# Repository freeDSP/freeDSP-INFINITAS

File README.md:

# freeDSP Infinitas

USB Audio Class 2 compliant audio interface with up to 32 input and up to 32 output channels and optional ADAU1452 DSP.

BOARD STATUS: RELEASED!

MAIN COORDINATOR: [dspverden](https://github.com/dspverden)

DOCUMENTATION: [Getting Started](https://docs.google.com/document/d/1jxKOcB1Af_6xawysrgFLgatrspSJ-aYZdDhTxlWoG2I)

IMPORTANT:

Please take care on which branch you're currently working!

Branches:

master - this branch always holds the latest released revision

develop - this is the develop branch with new features

## License
This work is licensed under <br />Dieses Werk ist lizenziert unter einer <a rel="license" href="http://creativecommons.org/licenses/by-nc-sa/4.0/">Creative Commons Namensnennung - Nicht-kommerziell - Weitergabe unter gleichen Bedingungen 4.0 International Lizenz</a>.

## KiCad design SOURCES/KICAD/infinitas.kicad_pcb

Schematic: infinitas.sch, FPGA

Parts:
B101, B102, B103, B104, B105, B106: TEST_1P; MountingHole_3.2mm_M3_DIN965_Pad
C101, C103, C104, C105, C106, C107, C108, C109, C110, C111, C112, C113, C114, C115, C116, C117, C118, C119, C120, C121, C124, C126, C129, C132: CAP_100n_50V_X7R_0805; C0805-X7R; digikey 399-1170-1-ND
C102, C122, C125, C127, C128, C130, C131, C133: CAP_10u0_25V_X5R_0805; C0805-X7R; digikey 490-10748-1-ND
C123: CAP_22u0_10V_X5R_0805; C0805-X7R; digikey 490-10511-1-ND
IC101: IC_CS2100CP; MSOP-10_3x3mm_Pitch0.5mm; digikey 598-1750-ND
IC102, IC103: IC_PCA9545APW; TSSOP-20_4.4x6.5mm_Pitch0.65mm; digikey 568-1865-1-ND
IC104: IC_LCMXO2-1200HC-6TG144C; TQFP-144_20x20mm_Pitch0.5mm; digikey 220-2040-ND
IC105: IC_TLV62565; SOT-23-5; digikey 296-43657-1-ND
IC106: IC_ADM811TARTZ; SOT-143; digikey ADM811TARTZ-REELCT-ND
IC107: IC_LM1117MP-5.0; SOT223; digikey LM1117MP-5.0/NOPBCT-ND
IC108, IC109: IC_NCP1117LPST33; SOT223; digikey NCP1117LPST33T3GOSCT-ND
L101: IND_2U20_30%_4A5; MCSDRH73B; digikey 811-1157-1-ND
OSC101: OSC_24M576; ASFL1; digikey 300-8253-1-ND
R101: RES_10K0_1%_0.125W_Thick_0805; C0805-RES; digikey 311-10.0KCRCT-ND
R102, R103, R104, R105, R112, R113, R114, R115, R124, R125, R126, R127, R134, R135, R136, R137: RES_2K00_1%_0.125W_Thick_0805; C0805-RES; digikey 311-2.00KCRCT-ND
R106, R107, R108, R109, R110, R111, R128, R129, R130, R131, R132, R133: RES_47K0_1%_0.125W_Thick_0805; C0805-RES; digikey 311-47.0KCRCT-ND
R116, R117, R122, R142, R144, R146, R149: RES_51R0_1%_0.125W_Thick_0805; C0805-RES; digikey 311-51.0CRCT-ND
R118: RES_4K70_1%_0.125W_Thick_0805; C0805-RES; digikey 311-4.70KCRCT-ND
R119, R120, R121, R123, R138, R139, R140, R141, R143, R145, R147, R148, R150, R151, R152: RES_51R0_5%_4x0603; R_Array_Convex_4x0603; digikey TC164J-51CT-ND
R153: RES_1K00_1%_0.125W_Thick_0805; C0805-RES; digikey 311-1.00KCRCT-ND
R154: RES_80K6_1%_0.125W_Thick_0805; C0805-RES; digikey 311-80.6KCRCT-ND
R155: RES_100K_1%_0.125W_Thick_0805; C0805-RES; digikey 311-100KCRCT-ND
R156: RES_120K_1%_0.125W_Thick_0805; C0805-RES; digikey 311-120KCRCT-ND
X101: CON_HDR_02x04; HDR_02x04; digikey 952-3276-ND
X102, X103: CON_IDC64; IDC64; digikey ED10532-ND
X104: CON_MicroMatch-10G; MM-10G; digikey A110869-ND
X105: CON_MicroFit3_02x02; Microfit3_43045-0428; digikey WM10670-ND

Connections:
+1V0: C123.1, L101.2, R154.1; also elsewhere on the board
+3V3: C101.2, C102.2, C103.2, C104.2, C106.2, C107.2, C108.2, C109.2, C110.2, C111.2, C112.2, C113.2, C114.2, C115.2, C116.2, C117.2, C118.2, C119.2, C120.2, C121.2, C132.2, C133.2, IC101.1, IC102.2, IC102.20, IC104.7, IC104.16, IC104.30, IC104.36, IC104.37, IC104.51, IC104.66, IC104.72, IC104.79, IC104.88, IC104.102, IC104.108, IC104.118, IC104.123, IC104.135, IC104.144, IC109.2, IC109.4, OSC101.4, R101.2, R102.2, R103.2, R104.2, R105.2, R106.2, R107.2, R108.2, R109.2, R110.2, R111.2, R112.2, R113.2, R114.2, R115.2, X101.5, X101.7; also elsewhere on the board
+5V: C122.2, C126.2, C127.2, IC105.1, IC105.4, IC107.2, IC107.4, X104.1, X104.2; also elsewhere on the board
+12V: C125.2, C128.2, C131.2, IC107.3, IC108.3, IC109.3, X102.1, X102.17, X102.33, X102.49, X103.1, X103.17, X103.33, X103.49, X105.1, X105.2
/BCLK:1: R143.6, X102.7
/BCLK:2: R152.6, X103.7
/BCLK:3: R141.6, X102.23
/BCLK:4: R148.6, X103.23
/BCLK:5: R139.6, X102.39
/BCLK:6: R147.6, X103.39
/BCLK:7: R123.6, X102.55
/BCLK:8: R145.6, X103.55
/BCLKIN0: R119.4; also elsewhere on the board
/BCLKIN1: R119.1; also elsewhere on the board
/BCLKIN2: R120.2; also elsewhere on the board
/BCLKIN3: R121.3; also elsewhere on the board
/BCLKOUT0: R140.7; also elsewhere on the board
/BCLKOUT1: R140.5; also elsewhere on the board
/BCLKOUT2: R138.7; also elsewhere on the board
/BCLKOUT3: R138.5; also elsewhere on the board
/CLKREF: IC101.7, R144.1
/LRCK:1: R143.7, X102.9
/LRCK:2: R152.7, X103.9
/LRCK:3: R141.7, X102.25
/LRCK:4: R148.7, X103.25
/LRCK:5: R139.7, X102.41
/LRCK:6: R147.7, X103.41
/LRCK:7: R123.7, X102.57
/LRCK:8: R145.7, X103.57
/LRCKIN0: R119.3; also elsewhere on the board
/LRCKIN1: R120.4; also elsewhere on the board
/LRCKIN2: R120.1; also elsewhere on the board
/LRCKIN3: R121.2; also elsewhere on the board
/LRCKOUT0: R140.8; also elsewhere on the board
/LRCKOUT1: R140.6; also elsewhere on the board
/LRCKOUT2: R138.8; also elsewhere on the board
/LRCKOUT3: R138.6; also elsewhere on the board
/MCLK: R142.1; also elsewhere on the board
/MCLK:1: R143.8, X102.15
/MCLK:2: R152.8, X103.15
/MCLK:3: R141.8, X102.31
/MCLK:4: R148.8, X103.31
/MCLK:5: R139.8, X102.47
/MCLK:6: R147.8, X103.47
/MCLK:7: R123.8, X102.63
/MCLK:8: R145.8, X103.63
/MDI:1: IC104.91, X102.3
/MDI:2: IC104.61, X103.3
/MDI:3: IC104.96, X102.19
/MDI:4: IC104.69, X103.19
/MDI:5: IC104.104, X102.35
/MDI:6: IC104.75, X103.35
/MDI:7: IC104.110, X102.51
/MDI:8: IC104.82, X103.51
/MDO:1: R143.5, X102.5
/MDO:2: R152.5, X103.5
/MDO:3: R141.5, X102.21
/MDO:4: R148.5, X103.21
/MDO:5: R139.5, X102.37
/MDO:6: R147.5, X103.37
/MDO:7: R123.5, X102.53
/MDO:8: R145.5, X103.53
/OSC: IC104.19, R117.2
/PLLCLK: IC104.27, R116.1
/PLLLOCKED: IC101.4, IC104.28
/SCL: IC101.9, IC102.18, IC103.18, IC104.126; also elsewhere on the board
/SCL:1: IC102.16, R112.1, X102.13
/SCL:2: IC103.13, R136.1, X103.13
/SCL:3: IC102.13, R114.1, X102.29
/SCL:4: IC103.16, R134.1, X103.29
/SCL:5: IC102.9, R102.1, X102.45
/SCL:6: IC103.6, R126.1, X103.45
/SCL:7: IC102.6, R104.1, X102.61
/SCL:8: IC103.9, R124.1, X103.61
/SDA: IC101.10, IC102.19, IC103.19, IC104.125; also elsewhere on the board
/SDA:1: IC102.15, R113.1, X102.11
/SDA:2: IC103.12, R137.1, X103.11
/SDA:3: IC102.12, R115.1, X102.27
/SDA:4: IC103.15, R135.1, X103.27
/SDA:5: IC102.8, R103.1, X102.43
/SDA:6: IC103.5, R127.1, X103.43
/SDA:7: IC102.5, R105.1, X102.59
/SDA:8: IC103.8, R125.1, X103.59
/SPDIFIN: IC104.48, X104.9
/SPDIFOUT: R150.5, X104.7
/TCK: IC104.131, R118.2, X101.3
/TDI: IC104.136, X101.1
/TDMIN0: R119.2; also elsewhere on the board
/TDMIN1: R120.3; also elsewhere on the board
/TDMIN2: R121.4; also elsewhere on the board
/TDMIN3: R121.1; also elsewhere on the board
/TDMOUT0: IC104.12; also elsewhere on the board
/TDMOUT1: IC104.11; also elsewhere on the board
/TDMOUT2: IC104.143; also elsewhere on the board
/TDMOUT3: IC104.142; also elsewhere on the board
/TDO: IC104.137, X101.6
/TMS: IC104.130, X101.4
/WCLKIN: IC104.59, X104.5
/WCLKOUT: R149.1, X104.3
/WCLKREF: IC101.5, R146.1
/XBCLK: R151.7; also elsewhere on the board
/XLRCK: R151.8; also elsewhere on the board
/XMCLK: R150.6; also elsewhere on the board
/XTDMIN1: R151.6; also elsewhere on the board
/XTDMIN2: R151.5; also elsewhere on the board
/XTDMIN3: R150.8; also elsewhere on the board
/XTDMIN4: R150.7; also elsewhere on the board
/XTDMOUT1: IC104.43; also elsewhere on the board
/XTDMOUT2: IC104.44; also elsewhere on the board
/XTDMOUT3: IC104.45; also elsewhere on the board
/XTDMOUT4: IC104.47; also elsewhere on the board
/dspSPDIFIN: R122.1; also elsewhere on the board
/dspSPDIFOUT: IC104.115; also elsewhere on the board
/~RST: IC104.42, IC106.2, R155.2; also elsewhere on the board
/~USBRST: R153.1; also elsewhere on the board
GND: C101.1, C102.1, C103.1, C104.1, C105.1, C106.1, C107.1, C108.1, C109.1, C110.1, C111.1, C112.1, C113.1, C114.1, C115.1, C116.1, C117.1, C118.1, C119.1, C120.1, C121.1, C122.1, C123.2, C124.1, C125.1, C126.1, C127.1, C128.1, C129.1, C130.1, C131.1, C132.1, C133.1, IC101.2, IC101.8, IC102.1, IC102.10, IC103.1, IC103.2, IC103.10, IC104.8, IC104.18, IC104.29, IC104.46, IC104.53, IC104.64, IC104.80, IC104.90, IC104.101, IC104.116, IC104.124, IC104.134, IC105.2, IC106.1, IC107.1, IC108.1, IC109.1, OSC101.2, R118.1, R155.1, R156.1, X101.8, X102.2, X102.4, X102.6, X102.8, X102.10, X102.12, X102.14, X102.16, X102.18, X102.20, X102.22, X102.24, X102.26, X102.28, X102.30, X102.32, X102.34, X102.36, X102.38, X102.40, X102.42, X102.44, X102.46, X102.48, X102.50, X102.52, X102.54, X102.56, X102.58, X102.60, X102.62, X102.64, X103.2, X103.4, X103.6, X103.8, X103.10, X103.12, X103.14, X103.16, X103.18, X103.20, X103.22, X103.24, X103.26, X103.28, X103.30, X103.32, X103.34, X103.36, X103.38, X103.40, X103.42, X103.44, X103.46, X103.48, X103.50, X103.52, X103.54, X103.56, X103.58, X103.60, X103.62, X103.64, X104.4, X104.6, X104.8, X104.10, X105.3, X105.4; also elsewhere on the board
unnamed: IC101.3, R116.2
unnamed: IC102.3, R108.1
unnamed: IC102.4, R107.1
unnamed: IC102.7, R106.1
unnamed: IC102.11, R111.1
unnamed: IC102.14, R110.1
unnamed: IC102.17, R109.1
unnamed: IC103.3, R130.1
unnamed: IC103.4, R129.1
unnamed: IC103.7, R128.1
unnamed: IC103.11, R133.1
unnamed: IC103.14, R132.1
unnamed: IC103.17, R131.1
unnamed: IC104.1, R138.4
unnamed: IC104.2, R138.3
unnamed: IC104.3, R138.2
unnamed: IC104.4, R138.1
unnamed: IC104.5, R140.4
unnamed: IC104.6, R140.3
unnamed: IC104.9, R140.2
unnamed: IC104.10, R140.1
unnamed: IC104.13, R142.2
unnamed: IC104.20, R144.2
unnamed: IC104.32, R146.2
unnamed: IC104.49, R150.4
unnamed: IC104.50, R150.3
unnamed: IC104.52, R150.2
unnamed: IC104.54, R150.1
unnamed: IC104.55, R151.4
unnamed: IC104.56, R151.3
unnamed: IC104.57, R151.2
unnamed: IC104.58, R151.1
unnamed: IC104.60, R149.2
unnamed: IC104.62, R152.4
unnamed: IC104.65, R152.3
unnamed: IC104.67, R152.2
unnamed: IC104.68, R152.1
unnamed: IC104.70, R148.4
unnamed: IC104.71, R148.3
unnamed: IC104.73, R148.2
unnamed: IC104.74, R148.1
unnamed: IC104.76, R147.4
unnamed: IC104.77, R147.3
unnamed: IC104.78, R147.2
unnamed: IC104.81, R147.1
unnamed: IC104.83, R145.4
unnamed: IC104.84, R145.3
unnamed: IC104.85, R145.2
unnamed: IC104.86, R145.1
unnamed: IC104.92, R143.4
unnamed: IC104.93, R143.3
unnamed: IC104.94, R143.2
unnamed: IC104.95, R143.1
unnamed: IC104.97, R141.4
unnamed: IC104.98, R141.3
unnamed: IC104.99, R141.2
unnamed: IC104.100, R141.1
unnamed: IC104.105, R139.4
unnamed: IC104.106, R139.3
unnamed: IC104.107, R139.2
unnamed: IC104.109, R139.1
unnamed: IC104.111, R123.4
unnamed: IC104.112, R123.3
unnamed: IC104.113, R123.2
unnamed: IC104.114, R123.1
unnamed: IC104.117, R122.2
unnamed: IC104.119, R121.8
unnamed: IC104.120, R121.7
unnamed: IC104.121, R121.6
unnamed: IC104.122, R121.5
unnamed: IC104.127, R120.8
unnamed: IC104.128, R120.7
unnamed: IC104.132, R120.6
unnamed: IC104.133, R120.5
unnamed: IC104.138, R119.8
unnamed: IC104.139, R119.7
unnamed: IC104.140, R119.6
unnamed: IC104.141, R119.5
unnamed: IC105.3, L101.1
unnamed: IC105.5, R154.2, R156.2
unnamed: IC106.3, R153.2
unnamed: OSC101.1, R101.1
unnamed: OSC101.3, R117.1
VDD: C105.2, C124.2, C129.2, C130.2, IC103.20, IC106.4, IC108.2, IC108.4, R124.2, R125.2, R126.2, R127.2, R128.2, R129.2, R130.2, R131.2, R132.2, R133.2, R134.2, R135.2, R136.2, R137.2; also elsewhere on the board

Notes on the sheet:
I2C_ADDR: 0xE2
I2C_ADDR: 0xE0

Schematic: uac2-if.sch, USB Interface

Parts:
C201: CAP_10n0_50V_X7R_0805; C0805-X7R; digikey 311-1136-1-ND
C202, C203, C204, C207: CAP_100n_50V_X7R_0805; C0805-X7R; digikey 399-1170-1-ND
C205, C206: CAP_10u0_25V_X5R_0805; C0805-X7R; digikey 490-10748-1-ND
C208: CAP_1n00_50V_X7R_0805; C0805-X7R; digikey 399-1147-1-ND
C209, C210, C211, C212, C213, C214, C215, C216, C217, C218, C219, C220, C221, C222, C223, C224, C225, C226, C227, C228, C229, C230, C231, C232, C233: CAP_100n_10V_X7R_0402; C_0402; digikey 490-6321-1-ND
D201: DIO_MBR120VLSFT; SOD123; digikey MBR120VLSFT3GOSCT-ND
IC201: IC_XE216-512-TQ128; TQFP-128_14x14mm_Pitch0.4mm_EP_Handsoldering; digikey 880-1096-ND
IC202: IC_NCP4681DSQ25T1G; SC-70-5; digikey NCP4681DSQ25T1GOSCT-ND
IC203: IC_IS25LP080D; SOIC8_3.9x4.9mm_Pitch1.27mm; digikey 706-1580-ND
IC204: IC_NC7WZ07; SC-70-6; digikey NC7WZ07P6XCT-ND
OSC201: OSC_24M0; ASFL1; digikey 300-8252-1-ND
R201, R213, R214: RES_10K0_1%_0.125W_Thick_0805; C0805-RES; digikey 311-10.0KCRCT-ND
R202, R205, R206, R209, R210: RES_51R0_1%_0.125W_Thick_0805; C0805-RES; digikey 311-51.0CRCT-ND
R203: RES_4R70_1%_0.125W_Thick_0805; C0805-RES; digikey 311-4.70CRCT-ND
R204: RES_51R0_5%_4x0603; R_Array_Convex_4x0603; digikey TC164J-51CT-ND
R207: RES_1K00_1%_0.125W_Thick_0805; C0805-RES; digikey 311-1.00KCRCT-ND
R208: RES_43R2_1%_0.125W_Thick_0805; C0805-RES; digikey P43.2CCT-ND
R211, R212: RES_2K00_1%_0.125W_Thick_0805; C0805-RES; digikey 311-2.00KCRCT-ND
R215: RES_100K_1%_0.125W_Thick_0805; C0805-RES; digikey 311-100KCRCT-ND
X201: CON_HDR_02x10; HDR_02x10; digikey S2011EC-10-ND
X202: CON_USB_B; USB_B; digikey ED2983-ND
X203: CON_HDR_01x04; HDR_01x04; digikey 732-5317-ND

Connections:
+1V0: C209.1, C210.1, C211.1, C212.1, C213.1, C214.1, C215.1, C216.1, C217.1, C218.1, C219.1, C220.1, C221.1, C222.1, IC201.11, IC201.16, IC201.17, IC201.24, IC201.36, IC201.41, IC201.49, IC201.56, IC201.60, IC201.73, IC201.80, IC201.81, IC201.87, IC201.101, IC201.102, IC201.120, IC201.126, R203.2; also elsewhere on the board
+2V5: C206.2, C233.1, IC201.110, IC201.111, IC202.4
+5V: C205.2, IC202.1, IC202.5; also elsewhere on the board
/SCL: IC201.37, R211.1; also elsewhere on the board
/SDA: IC201.38, R212.1; also elsewhere on the board
/UAC2 Interface/24M: IC201.125, R202.1
/UAC2 Interface/QSPI_D0: IC201.31, IC203.5
/UAC2 Interface/QSPI_D1: IC201.33, IC203.2
/UAC2 Interface/QSPI_D2: IC201.34, IC203.3
/UAC2 Interface/QSPI_D3: IC201.35, IC203.7
/UAC2 Interface/RST_N: IC201.123, IC201.124, IC204.4, IC204.6, R214.1
/UAC2 Interface/SPI_CLK: IC201.28, IC203.6
/UAC2 Interface/SPI_CS: IC201.27, IC203.1, R207.2
/UAC2 Interface/TCK: IC201.128, X201.9
/UAC2 Interface/TDI: IC201.2, X201.5
/UAC2 Interface/TDO: IC201.1, X201.13
/UAC2 Interface/TMS: IC201.127, X201.7
/UAC2 Interface/USBD_N: IC201.47, X202.2, X203.2
/UAC2 Interface/USBD_P: IC201.46, X202.3, X203.3
/UAC2 Interface/VBUS: C207.2, D201.1, IC201.45, R215.2
/UAC2 Interface/XL_DN0: IC201.9, X201.14
/UAC2 Interface/XL_DN1: IC201.8, X201.18
/UAC2 Interface/XL_UP0: R205.2, X201.10
/UAC2 Interface/XL_UP1: R206.2, X201.6
/UAC2 Interface/XSYS_RST_N: IC204.3, X201.15
/XBCLK: R209.2; also elsewhere on the board
/XLRCK: R210.2; also elsewhere on the board
/XMCLK: IC201.13, IC201.66; also elsewhere on the board
/XTDMIN1: IC201.88; also elsewhere on the board
/XTDMIN2: IC201.89; also elsewhere on the board
/XTDMIN3: IC201.90; also elsewhere on the board
/XTDMIN4: IC201.91; also elsewhere on the board
/XTDMOUT1: R204.4; also elsewhere on the board
/XTDMOUT2: R204.3; also elsewhere on the board
/XTDMOUT3: R204.2; also elsewhere on the board
/XTDMOUT4: R204.1; also elsewhere on the board
/~RST: IC204.1, R213.1; also elsewhere on the board
GND: C201.1, C202.2, C203.1, C204.1, C205.1, C206.1, C207.1, C208.1, C209.2, C210.2, C211.2, C212.2, C213.2, C214.2, C215.2, C216.2, C217.2, C218.2, C219.2, C220.2, C221.2, C222.2, C223.2, C224.2, C225.2, C226.2, C227.2, C228.2, C229.2, C230.2, C231.2, C232.2, C233.2, IC201.104, IC201.129, IC202.3, IC203.4, OSC201.2, R208.1, R215.1, X201.4, X201.8, X201.12, X201.16, X201.20, X202.4, X203.4; also elsewhere on the board
unnamed: C202.1, IC201.103, R203.1
unnamed: C208.2, X202.5
unnamed: D201.2, X202.1, X203.1
unnamed: IC201.3, R204.8
unnamed: IC201.4, R204.7
unnamed: IC201.5, R204.6
unnamed: IC201.7, R204.5
unnamed: IC201.10, R205.1
unnamed: IC201.12, R206.1
unnamed: IC201.48, R208.2
unnamed: IC201.63, R209.1
unnamed: IC201.64, R210.1
unnamed: OSC201.1, R201.1
unnamed: OSC201.3, R202.2
VDD: C201.2, C203.2, C204.2, C223.1, C224.1, C225.1, C226.1, C227.1, C228.1, C229.1, C230.1, C231.1, C232.1, IC201.6, IC201.14, IC201.19, IC201.29, IC201.42, IC201.44, IC201.52, IC201.67, IC201.83, IC201.92, IC201.105, IC203.8, IC204.5, OSC201.4, R201.2, R207.1, R211.2, R212.2, R213.2, R214.2; also elsewhere on the board

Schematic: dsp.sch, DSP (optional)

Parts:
C301, C304, C308, C313: CAP_10u0_25V_X5R_0805; C0805-X7R; digikey 490-10748-1-ND
C302, C305, C307, C309, C310, C311, C312, C314, C315, C316, C317: CAP_100n_50V_X7R_0805; C0805-X7R; digikey 399-1170-1-ND
C303: CAP_5n60_50V_X7R_0805; C0805-X7R; digikey 311-1134-1-ND
C306: CAP_150p_50V_C0G_0805; C0805-X7R; digikey 399-1125-1-ND
FER301, FER302: FER_600R_600MA_0805; C0805-RES; digikey 490-1040-1-ND
IC301: IC_ADAU1452; QFP72_10x10_EP_Handsoldering; digikey ADAU1452WBCPZ-ND
IC302: IC_25AA1024; SOIJ8_5.3x5.3mm_P1.27mm; digikey 25AA1024T-I/SMCT-ND
JP301: CON_JUMPER; HDR_01x02; digikey 732-5315-ND
Q301: Q_STD2805; TO-252-2Lead; digikey 497-7465-1-ND
R301: RES_1K00_1%_0.125W_Thick_0805; C0805-RES; digikey 311-1.00KCRCT-ND
R302, R303, R304, R305, R306: RES_51R0_1%_0.125W_Thick_0805; C0805-RES; digikey 311-51.0CRCT-ND
R307: RES_4K32_1%_0.125W_Thick_0805; C0805-RES; digikey 311-4.32KCRCT-ND
R308, R313, R314: RES_10K0_1%_0.125W_Thick_0805; C0805-RES; digikey 311-10.0KCRCT-ND
R309, R310, R315, R316: DNP; C0805-RES
R311, R312, R317, R318: RES_0R00_1%_0.125W_Thick_0805; C0805-RES; digikey 311-0.0ARCT-ND
X301: CON_HDR_02x05; HDR_02x05; digikey 952-2117-ND

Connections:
+3V3: C307.2, C313.2, C314.2, C315.2, C316.2, C317.2, FER301.1, FER302.1, IC301.2, IC301.18, IC301.38, IC301.56, IC302.7, IC302.8, Q301.3, R301.1, R308.2, R309.1, R310.1, R313.1, R314.1; also elsewhere on the board
/BCLKIN0: IC301.57; also elsewhere on the board
/BCLKIN1: IC301.60; also elsewhere on the board
/BCLKIN2: IC301.65; also elsewhere on the board
/BCLKIN3: IC301.68; also elsewhere on the board
/BCLKOUT0: IC301.40; also elsewhere on the board
/BCLKOUT1: IC301.43; also elsewhere on the board
/BCLKOUT2: IC301.48; also elsewhere on the board
/BCLKOUT3: IC301.51; also elsewhere on the board
/DSP/MISO: R315.1, X301.5
/DSP/MOSI: IC301.32, R318.2, X301.8
/DSP/SCLK: R316.1, X301.7
/DSP/~SS: IC301.33, R317.2, X301.9
/LRCKIN0: IC301.58; also elsewhere on the board
/LRCKIN1: IC301.61; also elsewhere on the board
/LRCKIN2: IC301.66; also elsewhere on the board
/LRCKIN3: IC301.69; also elsewhere on the board
/LRCKOUT0: IC301.39; also elsewhere on the board
/LRCKOUT1: IC301.42; also elsewhere on the board
/LRCKOUT2: IC301.47; also elsewhere on the board
/LRCKOUT3: IC301.50; also elsewhere on the board
/MCLK: IC301.21; also elsewhere on the board
/SCL: R311.1; also elsewhere on the board
/SDA: R312.1; also elsewhere on the board
/TDMIN0: IC301.59; also elsewhere on the board
/TDMIN1: IC301.62; also elsewhere on the board
/TDMIN2: IC301.67; also elsewhere on the board
/TDMIN3: IC301.70; also elsewhere on the board
/TDMOUT0: R306.1; also elsewhere on the board
/TDMOUT1: R305.1; also elsewhere on the board
/TDMOUT2: R304.1; also elsewhere on the board
/TDMOUT3: R302.1; also elsewhere on the board
/dspSPDIFIN: IC301.4; also elsewhere on the board
/dspSPDIFOUT: R303.2; also elsewhere on the board
/~RST: IC301.24; also elsewhere on the board
/~USBRST: X301.6; also elsewhere on the board
GND: C301.1, C302.1, C304.1, C305.1, C307.1, C308.1, C309.1, C310.1, C311.1, C312.1, C313.1, C314.1, C315.1, C316.1, C317.1, IC301.1, IC301.6, IC301.14, IC301.17, IC301.19, IC301.25, IC301.36, IC301.37, IC301.54, IC301.55, IC301.72, IC301.73, IC302.4, JP301.2, R317.1, R318.1, X301.10; also elsewhere on the board
unnamed: C301.2, C302.2, FER301.2, IC301.7
unnamed: C303.1, C304.2, C305.2, C306.1, FER302.2, IC301.15
unnamed: C303.2, R307.1
unnamed: C306.2, IC301.16, R307.2
unnamed: IC301.3, Q301.1, R301.2
unnamed: IC301.5, R303.1
unnamed: IC301.26, IC302.1, R313.2
unnamed: IC301.27, IC302.5
unnamed: IC301.28, IC302.6
unnamed: IC301.29, IC302.2
unnamed: IC301.30, R309.2, R312.2, R315.2, X301.3
unnamed: IC301.31, R310.2, R311.2, R316.2, X301.1
unnamed: IC301.34, JP301.1, R308.1
unnamed: IC301.41, R306.2
unnamed: IC301.44, R305.2
unnamed: IC301.49, R304.2
unnamed: IC301.52, R302.2
unnamed: IC302.3, R314.2
VPP: C308.2, C309.2, C310.2, C311.2, C312.2, IC301.20, IC301.35, IC301.53, IC301.71, Q301.2

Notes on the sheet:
USBi connector
For SPI control by USBi - populate R315, R316 with 0R00 - do not populate R309, R310, R311, R312, R317, R318 For I2C control by USBi - populate R309, R310 with 2K00 - populate R317, R318 with 0R00 - do not populate R311, R312, R315, R316 For I2C control by XE216 - populate R311, R312, R317, R318 wi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

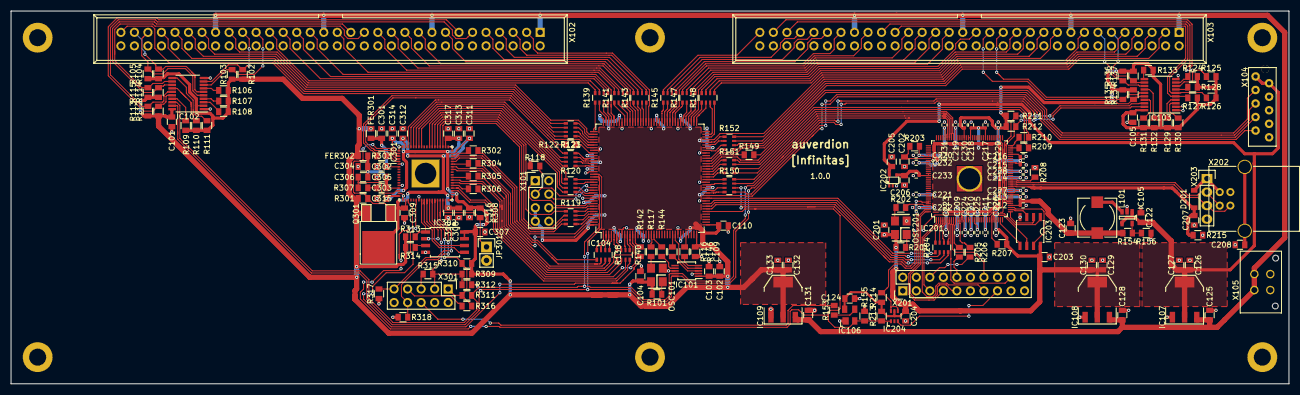
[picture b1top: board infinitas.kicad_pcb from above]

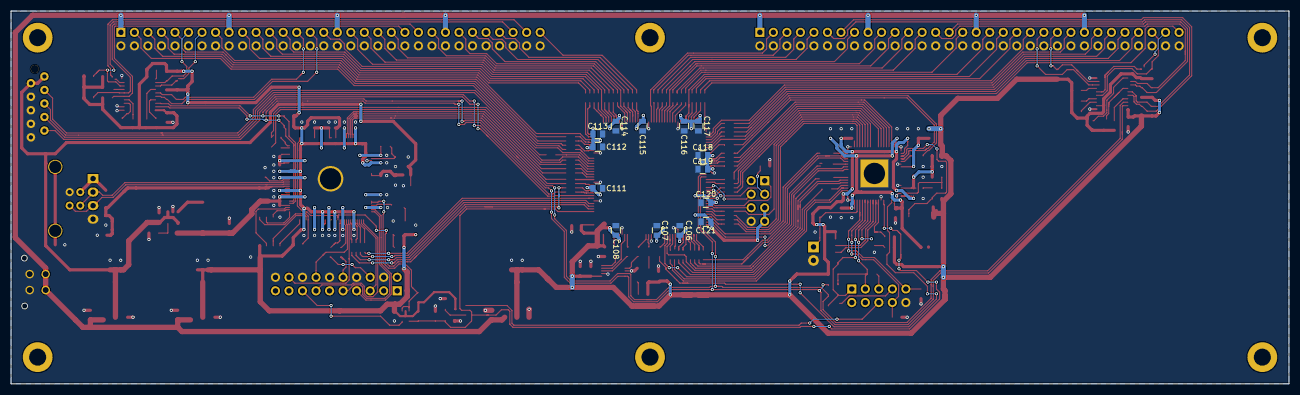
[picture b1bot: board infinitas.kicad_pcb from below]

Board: 2 copper layers, 240.0 x 70.0 mm, 210 parts (14 on the bottom side), 258 nets.

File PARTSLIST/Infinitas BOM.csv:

Reference, Quantity, Value, Footprint, Datasheet, Value1, Value2, digikey
B101 B102 B103 B104 B105 B106 ,6,"TEST_1P","rklib:MountingHole_3.2mm_M3_DIN965_Pad","","-","-","-"
C102 C122 C125 C127 C128 C130 C131 C133 C205 C206 C301 C304 C308 C313 ,14,"CAP_10u0_25V_X5R_0805","rklib:C0805-X7R","","10u0","20% 25V X5R","490-10748-1-ND"
C101 C103 C104 C105 C106 C107 C108 C109 C110 C111 C112 C113 C114 C115 C116 C117 C118 C119 C120 C121 C124 C126 C129 C132 C202 C203 C204 C207 C302 C305 C307 C309 C310 C311 C312 C314 C315 C316 C317 ,39,"CAP_100n_50V_X7R_0805","rklib:C0805-X7R","","100n","5% 50V X7R","399-1170-1-ND"
C123 ,1,"CAP_22u0_10V_X5R_0805","rklib:C0805-X7R","","22u0","20% 10V X5R","490-10511-1-ND"
C201 ,1,"CAP_10n0_50V_X7R_0805","rklib:C0805-X7R","","10n0","10% 50V X7R","311-1136-1-ND"
C208 ,1,"CAP_1n00_50V_X7R_0805","rklib:C0805-X7R","","1n00","10% 50V X7R","399-1147-1-ND"
C209 C210 C211 C212 C213 C214 C215 C216 C217 C218 C219 C220 C221 C222 C223 C224 C225 C226 C227 C228 C229 C230 C231 C232 C233 ,25,"CAP_100n_10V_X7R_0402","Capacitors_SMD:C_0402","","100n","10% 10V X7R","490-6321-1-ND"
C303 ,1,"CAP_5n60_50V_X7R_0805","rklib:C0805-X7R","","5n60","10% 50V X7R","311-1134-1-ND"
C306 ,1,"CAP_150p_50V_C0G_0805","rklib:C0805-X7R","","150p","5% 50V C0G","399-1125-1-ND"
D201 ,1,"DIO_MBR120VLSFT","rklib:SOD123","","MBR120VLSFT","Schottky 20V 1 A ","MBR120VLSFT3GOSCT-ND"
FER301 FER302 ,2,"FER_600R_600MA_0805","rklib:C0805-RES","","600R","@100MHz 600mA","490-1040-1-ND"
IC101 ,1,"IC_CS2100CP","Housings_SSOP:MSOP-10_3x3mm_Pitch0.5mm","","CS2100CP","Fractional-N Clock Multiplier","598-1750-ND"
IC102 IC103 ,2,"IC_PCA9545APW","Housings_SSOP:TSSOP-20_4.4x6.5mm_Pitch0.65mm","","PCA9545APW","I2C Switch 4ch","568-1865-1-ND"
IC104 ,1,"IC_LCMXO2-1200HC-6TG144C","Housings_QFP:TQFP-144_20x20mm_Pitch0.5mm","","LCMXO2-1200HC-6TG144C","FPGA","220-2040-ND"
IC105 ,1,"IC_TLV62565","TO_SOT_Packages_SMD:SOT-23-5","","TLV62565","1.5A","296-43657-1-ND"
IC106 ,1,"IC_ADM811TARTZ","TO_SOT_Packages_SMD:SOT-143","","ADM811TARTZ","Spannungsmonitor","ADM811TARTZ-REELCT-ND"
IC107 ,1,"IC_LM1117MP-5.0","rklib:SOT223","","LM1117MP-5.0","LDO","LM1117MP-5.0/NOPBCT-ND"
IC108 IC109 ,2,"IC_NCP1117LPST33","rklib:SOT223","","NCP1117LPST33","LDO","NCP1117LPST33T3GOSCT-ND"
IC201 ,1,"IC_XE216-512-TQ128","rklib:TQFP-128_14x14mm_Pitch0.4mm_EP_Handsoldering","","XE216-512-TQ128","xCore","880-1096-ND"
IC202 ,1,"IC_NCP4681DSQ25T1G","TO_SOT_Packages_SMD:SC-70-5","","NCP4681DSQ25T1G","2,5V 150mA","NCP4681DSQ25T1GOSCT-ND"
IC203 ,1,"IC_IS25LP080D","rklib:SOIC8_3.9x4.9mm_Pitch1.27mm","","IS25LP080D","8Mb","706-1580-ND"
IC204 ,1,"IC_NC7WZ07","TO_SOT_Packages_SMD:SC-70-6","","NC7WZ07","Noninverting Buffer","NC7WZ07P6XCT-ND"
IC301 ,1,"IC_ADAU1452","rklib:QFP72_10x10_EP_Handsoldering","","ADAU1452","-","ADAU1452WBCPZ-ND"
IC302 ,1,"IC_25AA1024","Housings_SOIC:SOIJ-8_5.3x5.3mm_Pitch1.27mm","","25AA1024","1Mbit","25AA1024T-I/SMCT-ND"
JP301 ,1,"CON_JUMPER","rklib:HDR_01x02","","Jumper"," -","732-5315-ND"
L101 ,1,"IND_2U20_30%_4A5","rklib:MCSDRH73B","","2u20","30% 4.5A 26 mOhm","811-1157-1-ND"
OSC101 ,1,"OSC_24M576","rklib:ASFL1","","24M576","-","300-8253-1-ND"
OSC201 ,1,"OSC_24M0","rklib:ASFL1","","24M0","-","300-8252-1-ND"
Q301 ,1,"Q_STD2805","TO_SOT_Packages_SMD:TO-252-2Lead","","STD2805","PNP 60V 5A 150MHz 15W ","497-7465-1-ND"
R101 R201 R213 R214 R308 R313 R314 ,7,"RES_10K0_1%_0.125W_Thick_0805","rklib:C0805-RES","","10K0","1% 0.125W Thick","311-10.0KCRCT-ND"
R118 ,1,"RES_4K70_1%_0.125W_Thick_0805","rklib:C0805-RES","","4K70","1% 0.125W Thick","311-4.70KCRCT-ND"
R102 R103 R104 R105 R112 R113 R114 R115 R124 R125 R126 R127 R134 R135 R136 R137 R211 R212 ,18,"RES_2K00_1%_0.125W_Thick_0805","rklib:C0805-RES","","2K00","1% 0.125W Thick","311-2.00KCRCT-ND"
R106 R107 R108 R109 R110 R111 R128 R129 R130 R131 R132 R133 ,12,"RES_47K0_1%_0.125W_Thick_0805","rklib:C0805-RES","","47K0","1% 0.125W Thick","311-47.0KCRCT-ND"
R119 R120 R121 R123 R138 R139 R140 R141 R143 R145 R147 R148 R150 R151 R152 R204 ,16,"RES_51R0_5%_4x0603","Resistors_SMD:R_Array_Convex_4x0603","","51R0","5% 62,5mW","TC164J-51CT-ND"
R116 R117 R122 R142 R144 R146 R149 R202 R205 R206 R209 R210 R302 R303 R304 R305 R306 ,17,"RES_51R0_1%_0.125W_Thick_0805","rklib:C0805-RES","","51R0","1% 0.125W Thick","311-51.0CRCT-ND"
R153 R207 R301 ,3,"RES_1K00_1%_0.125W_Thick_0805","rklib:C0805-RES","","1K00","1% 0.125W Thick","311-1.00KCRCT-ND"
R154 ,1,"RES_80K6_1%_0.125W_Thick_0805","rklib:C0805-RES","","80K6","1% 0.125W Thick","311-80.6KCRCT-ND"
R155 R215 ,2,"RES_100K_1%_0.125W_Thick_0805","rklib:C0805-RES","","100K","1% 0.125W Thick","311-100KCRCT-ND"
R156 ,1,"RES_120K_1%_0.125W_Thick_0805","rklib:C0805-RES","","120K","1% 0.125W Thick","311-120KCRCT-ND"
R203 ,1,"RES_4R70_1%_0.125W_Thick_0805","rklib:C0805-RES","","4R70","1% 0.125W Thick","311-4.70CRCT-ND"
R208 ,1,"RES_43R2_1%_0.125W_Thick_0805","rklib:C0805-RES","","43R2","1% 0.125W Thick","P43.2CCT-ND"
R307 ,1,"RES_4K32_1%_0.125W_Thick_0805","rklib:C0805-RES","","4K32","1% 0.125W Thick","311-4.32KCRCT-ND"
R309 R310 R315 R316 ,4,"DNP","rklib:C0805-RES","","DNP","-","-"
R311 R312 R317 R318 ,4,"RES_0R00_1%_0.125W_Thick_0805","rklib:C0805-RES","","0R00","1% 0.125W Thick","311-0.0ARCT-ND"
X101 ,1,"CON_HDR_02x04","rklib:HDR_02x04","","HDR-02x04","-","952-3276-ND"
X102 X103 ,2,"CON_IDC64","rklib:IDC64","","IDC64","-","ED10532-ND"
X104 ,1,"CON_MicroMatch-10G","rklib:MM-10G","","MicroMatch-10"," -","A110869-ND"
X105 ,1,"CON_MicroFit3_02x02","rklib:Microfit3_43045-0428","","MicroFit3 02x02","-","WM10670-ND"
X201 ,1,"CON_HDR_02x10","rklib:HDR_02x10","","HDR-02x10","-","S2011EC-10-ND"
X202 ,1,"CON_USB_B","rklib:USB_B","","USB_B","horizontal","ED2983-ND"
X203 ,1,"CON_HDR_01x04","rklib:HDR_01x04","","HDR-01x04","-","732-5317-ND"
X301 ,1,"CON_HDR_02x05","rklib:HDR_02x05","","HDR-02x05","-","952-2117-ND"
